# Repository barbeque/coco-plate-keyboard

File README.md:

## TRS-80 CoCo keyboard replacements
Here are some projects for keyboard replacements for the TRS-80 Colour Computer.

For more information on the project, please consult [the Leaded Solder blog post on the keyboard PCB](https://www.leadedsolder.com/2025/01/07/coco-mechanical-keyboard-build.html).

## Branches
### master
This branch contains a 3D printable plate for fly-wiring switches. It is not tested and not recommended for production.

### kicad-pcb
This branch contains a KiCad-developed PCB for mounting Gateron-style switches. It has been tested. You can [get the gerbers from the Releases page](https://github.com/barbeque/coco-plate-keyboard/releases).

## How to build
TODO

## License
These projects are licensed under the [CERN Open Hardware License, Strongly Reciprocal](https://spdx.org/licenses/CERN-OHL-S-2.0.html).

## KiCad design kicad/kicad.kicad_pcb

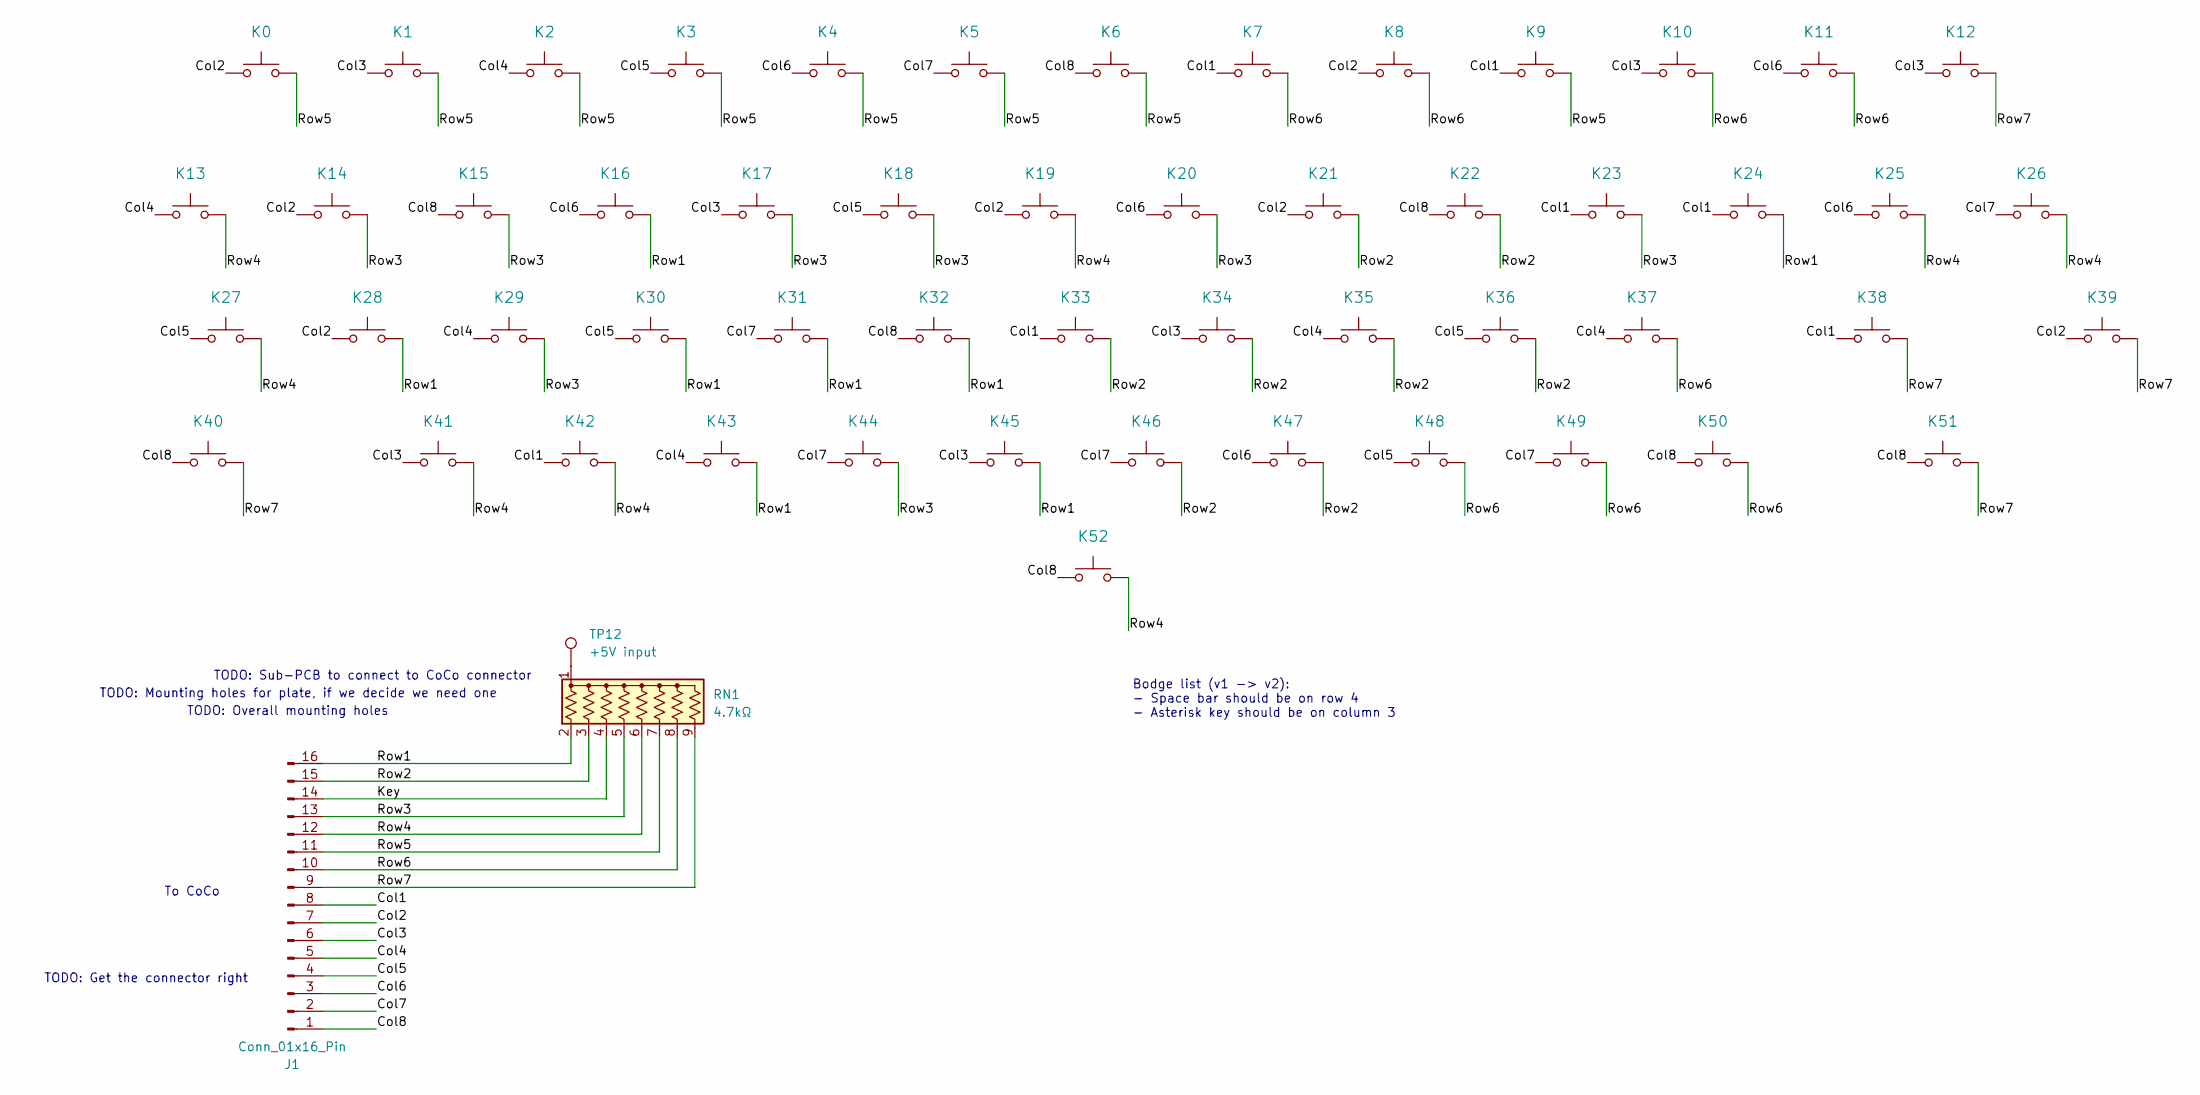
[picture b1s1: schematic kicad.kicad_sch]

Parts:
J1: Conn_01x16_Pin; PinSocket_1x16_P2.54mm_Horizontal
K0: !,,,,,,1; SW_Cherry_MX_1.00u_PCB
K1: ",,,,,,2; SW_Cherry_MX_1.00u_PCB
K2: #,,,,,,3; SW_Cherry_MX_1.00u_PCB
K3: $,,,,,,4; SW_Cherry_MX_1.00u_PCB
K4: %,,,,,,5; SW_Cherry_MX_1.00u_PCB
K5: &,,,,,,6; SW_Cherry_MX_1.00u_PCB
K6: ',,,,,,7; SW_Cherry_MX_1.00u_PCB
K7: (,,,,,,8; SW_Cherry_MX_1.00u_PCB
K8: ),,,,,,9; SW_Cherry_MX_1.00u_PCB
K9: 0; SW_Cherry_MX_1.00u_PCB
K10: *,,,,,,:; SW_Cherry_MX_1.00u_PCB
K11: =,,,,,,-; SW_Cherry_MX_1.00u_PCB
K12: Break; SW_Cherry_MX_1.00u_PCB
K13: Up; SW_Cherry_MX_1.00u_PCB
K14: Q; SW_Cherry_MX_1.00u_PCB
K15: W; SW_Cherry_MX_1.00u_PCB
K16: E; SW_Cherry_MX_1.00u_PCB
K17: R; SW_Cherry_MX_1.00u_PCB
K18: T; SW_Cherry_MX_1.00u_PCB
K19: Y; SW_Cherry_MX_1.00u_PCB
K20: U; SW_Cherry_MX_1.00u_PCB
K21: I; SW_Cherry_MX_1.00u_PCB
K22: O; SW_Cherry_MX_1.00u_PCB
K23: P; SW_Cherry_MX_1.00u_PCB
K24: @; SW_Cherry_MX_1.00u_PCB
K25: Left; SW_Cherry_MX_1.00u_PCB
K26: Right; SW_Cherry_MX_1.00u_PCB
K27: Down; SW_Cherry_MX_1.00u_PCB
K28: A; SW_Cherry_MX_1.00u_PCB
K29: S; SW_Cherry_MX_1.00u_PCB
K30: D; SW_Cherry_MX_1.00u_PCB
K31: F; SW_Cherry_MX_1.00u_PCB
K32: G; SW_Cherry_MX_1.00u_PCB
K33: H; SW_Cherry_MX_1.00u_PCB
K34: J; SW_Cherry_MX_1.00u_PCB
K35: K; SW_Cherry_MX_1.00u_PCB
K36: L; SW_Cherry_MX_1.00u_PCB
K37: +,,,,,,;; SW_Cherry_MX_1.00u_PCB
K38: ENTER; SW_Cherry_MX_2.25u_PCB
K39: CLEAR; SW_Cherry_MX_1.00u_PCB
K40, K51: SHIFT; SW_Cherry_MX_2.25u_PCB
K41: Z; SW_Cherry_MX_1.00u_PCB
K42: X; SW_Cherry_MX_1.00u_PCB
K43: C; SW_Cherry_MX_1.00u_PCB
K44: V; SW_Cherry_MX_1.00u_PCB
K45: B; SW_Cherry_MX_1.00u_PCB
K46: N; SW_Cherry_MX_1.00u_PCB
K47: M; SW_Cherry_MX_1.00u_PCB
K48: <,,,,,,,; SW_Cherry_MX_1.00u_PCB
K49: >,,,,,,.; SW_Cherry_MX_1.00u_PCB
K50: ?,,,,,,/; SW_Cherry_MX_1.00u_PCB
K52: Blank; SW_Cherry_MX_6.25u_PCB
RN1: 4.7kΩ; R_Array_SIP9
TP12: +5V input; PinHeader_1x01_P2.54mm_Horizontal

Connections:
/Col1: J1.8, K7.1, K9.1, K23.1, K24.1, K33.1, K38.1, K42.1
/Col2: J1.7, K0.1, K8.1, K14.1, K19.1, K21.1, K28.1, K39.1
/Col3: J1.6, K1.1, K10.1, K12.1, K17.1, K34.1, K41.1, K45.1
/Col4: J1.5, K2.1, K13.1, K29.1, K35.1, K37.1, K43.1
/Col5: J1.4, K3.1, K18.1, K27.1, K30.1, K36.1, K48.1
/Col6: J1.3, K4.1, K11.1, K16.1, K20.1, K25.1, K47.1
/Col7: J1.2, K5.1, K26.1, K31.1, K44.1, K46.1, K49.1
/Col8: J1.1, K6.1, K15.1, K22.1, K32.1, K40.1, K50.1, K51.1, K52.1
/Key: J1.14, RN1.4 (R3)
/Row1: J1.16, K16.2, K24.2, K28.2, K30.2, K31.2, K32.2, K43.2, K45.2, RN1.2 (R1)
/Row2: J1.15, K21.2, K22.2, K33.2, K34.2, K35.2, K36.2, K46.2, K47.2, RN1.3 (R2)
/Row3: J1.13, K14.2, K15.2, K17.2, K18.2, K20.2, K23.2, K29.2, K44.2, RN1.5 (R4)
/Row4: J1.12, K13.2, K19.2, K25.2, K26.2, K27.2, K41.2, K42.2, K52.2, RN1.6 (R5)
/Row5: J1.11, K0.2, K1.2, K2.2, K3.2, K4.2, K5.2, K6.2, K9.2, RN1.7 (R6)
/Row6: J1.10, K7.2, K8.2, K10.2, K11.2, K37.2, K48.2, K49.2, K50.2, RN1.8 (R7)
/Row7: J1.9, K12.2, K38.2, K39.2, K40.2, K51.2, RN1.9 (R8)
unnamed: RN1.1 (common), TP12.1

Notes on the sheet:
TODO: Get the connector right
To CoCo
TODO: Overall mounting holes
TODO: Sub-PCB to connect to CoCo connector
TODO: Mounting holes for plate, if we decide we need one
Bodge list (v1 -> v2): - Space bar should be on row 4 - Asterisk key should be on column 3

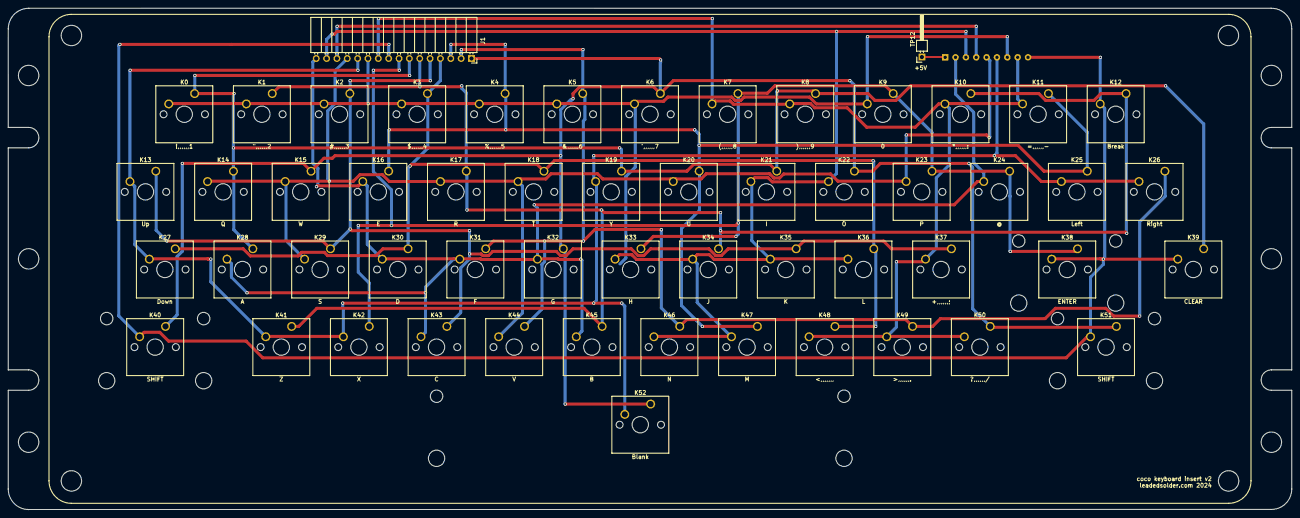
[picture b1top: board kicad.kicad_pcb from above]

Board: 2 copper layers, 315.0 x 123.0 mm, 56 parts (1 on the bottom side), 17 nets.

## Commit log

2020-01-05 Rough draft, with no measurements
2020-01-05 Trying to do DXF projection
2020-01-05 Generated DXF from that one generator
2020-01-07 The key layout from the editor
2020-01-07 Add bare radius before edge paddig
2020-01-07 Keyboard hole prototype
2020-01-07 Trying to push the keyboard holes closer to the edge
2020-01-07 I think the keyboard holes are aligned properly now...
2020-01-07 More plate fixing
2024-09-14 Add buildable JSON
2024-09-14 starting to lay out
2024-09-14 More rows, needs double-check
2024-09-15 Matrix laid out
2024-09-15 Diodes removed, mounts added
2024-09-15 Routed
2024-09-15 Re-route
2024-09-15 TODOs
2024-09-15 Terrible board outline
2024-09-15 Aligned
2024-09-15 Nice diagram
2024-09-15 Critical dimension checked, we're good to go
2024-09-15 Routed in the connector, although I need to double check
2024-09-15 Pin labels
2024-09-15 Mounting holes for eventual plate
2024-10-04 Remove slightly misleading pin-1 marking
2024-10-05 Bump entire keyboard usable area up a little bit
2024-10-05 Prepare v2 number
2024-10-10 Add F-board pull-up
2024-10-10 Fix Spacebar
2024-10-10 Fix asterisk key
2024-12-17 Produce v2 prototype gerbers for nickle241
2026-03-30 Add README
2026-03-30 OSHW
